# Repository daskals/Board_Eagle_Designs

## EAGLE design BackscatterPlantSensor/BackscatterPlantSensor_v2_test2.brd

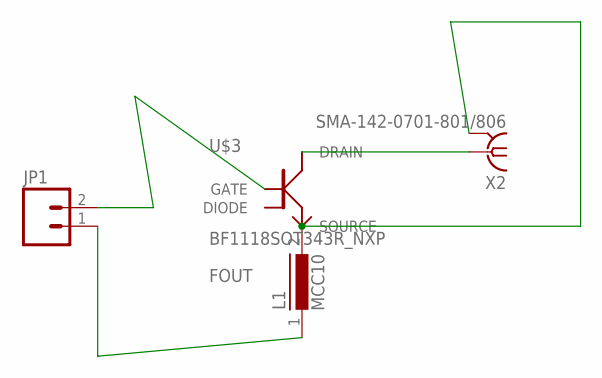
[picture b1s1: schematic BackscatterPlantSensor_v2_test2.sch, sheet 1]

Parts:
JP1: M02PTH; 1X02
L1: MCC10
U$3: BF1118SOT343R_NXP; SOT343R
X2: SMA-142-0701-801/806; J502-ND-142-0701-801/806

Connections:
DGND: JP1.2, U$3.1 (GATE)
DRAIN: U$3.4 (DRAIN), X2.1
FOUT: JP1.1, L1.1
FOUT2: L1.2, U$3.3 (SOURCE), X2.G@1 (GND)
GND: X2.G@2 (GND), X2.G@3 (GND), X2.G@4 (GND)

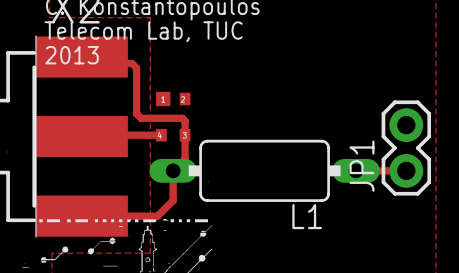
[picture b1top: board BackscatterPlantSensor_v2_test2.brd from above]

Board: 2 copper layers, 4 parts (0 on the bottom side), 5 nets.

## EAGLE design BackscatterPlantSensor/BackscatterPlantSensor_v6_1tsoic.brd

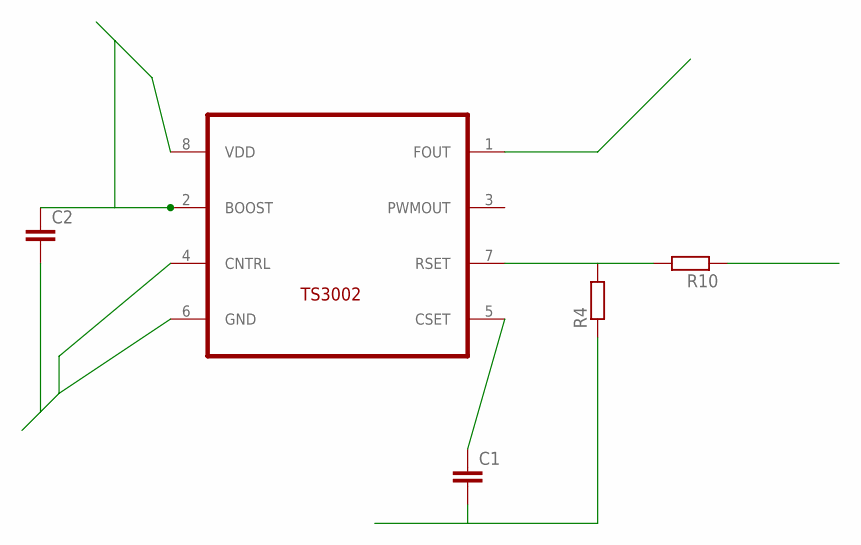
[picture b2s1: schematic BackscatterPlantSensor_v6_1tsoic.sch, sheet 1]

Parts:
C1, C2: CC0603; C0603
R4, R10: R-EU_R0603; R0603
U$1: TS3002; TDFN22-8

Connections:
DGND: C1.2, C2.2, R4.1, U$1.4 (CNTRL), U$1.6 (GND); also elsewhere on the board
FOUT: U$1.1 (FOUT); also elsewhere on the board
unnamed: C1.1, U$1.5 (CSET)
unnamed: R4.2, R10.2, U$1.7 (RSET)
VCOND: R10.1; also elsewhere on the board
VDD: C2.1, U$1.2 (BOOST), U$1.8 (VDD); also elsewhere on the board

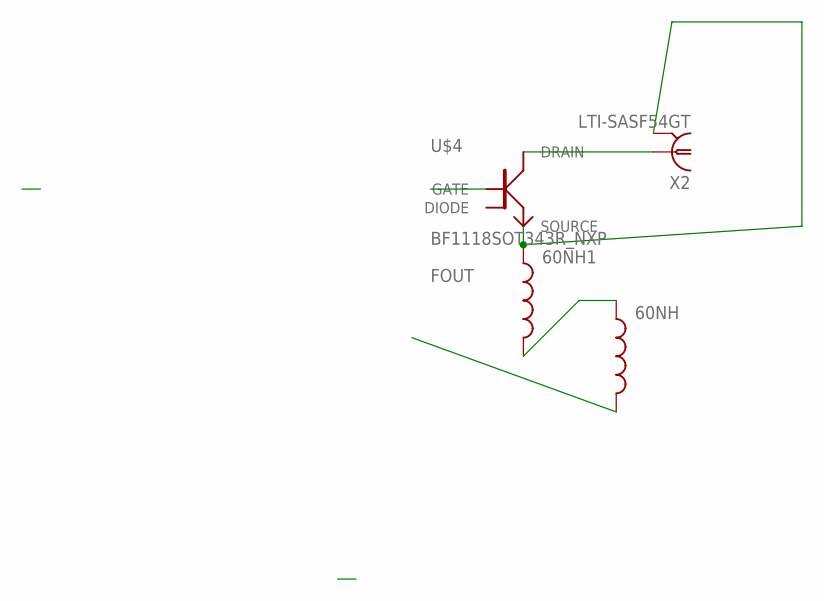
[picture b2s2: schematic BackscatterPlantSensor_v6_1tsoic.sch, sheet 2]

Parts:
60NH, 60NH1: INDUCTOR0402; C0402
U$4: BF1118SOT343R_NXP; SOT343R
X2: LTI-SASF54GT

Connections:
DGND: U$4.1 (GATE); also elsewhere on the board
DRAIN: U$4.4 (DRAIN), X2.1
FOUT: 60NH.2; also elsewhere on the board
FOUT2: 60NH1.1, U$4.3 (SOURCE), X2.2 (GND)
GND: X2.3 (GND), X2.4 (GND), X2.5 (GND); also elsewhere on the board
unnamed: 60NH.1, 60NH1.2

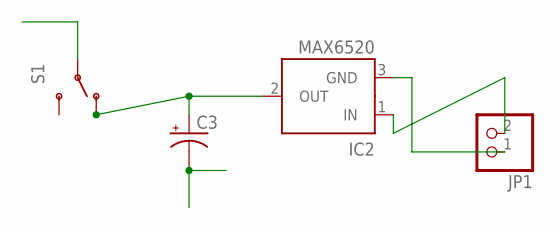
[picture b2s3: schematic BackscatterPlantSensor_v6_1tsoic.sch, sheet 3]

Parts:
C3: CAP_POL1206; EIA3216
IC2: MAX6520; SOT23
JP1: PINHD-1X2; 1X02
S1: SWITCH-SPDTPTH; SWITCH-SPDT

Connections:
GND: C3.C (-), IC2.3 (GND), JP1.1; also elsewhere on the board
unnamed: IC2.1 (IN), JP1.2
unnamed: C3.A (+), IC2.2 (OUT), S1.1 (O)
VDD: S1.2; also elsewhere on the board

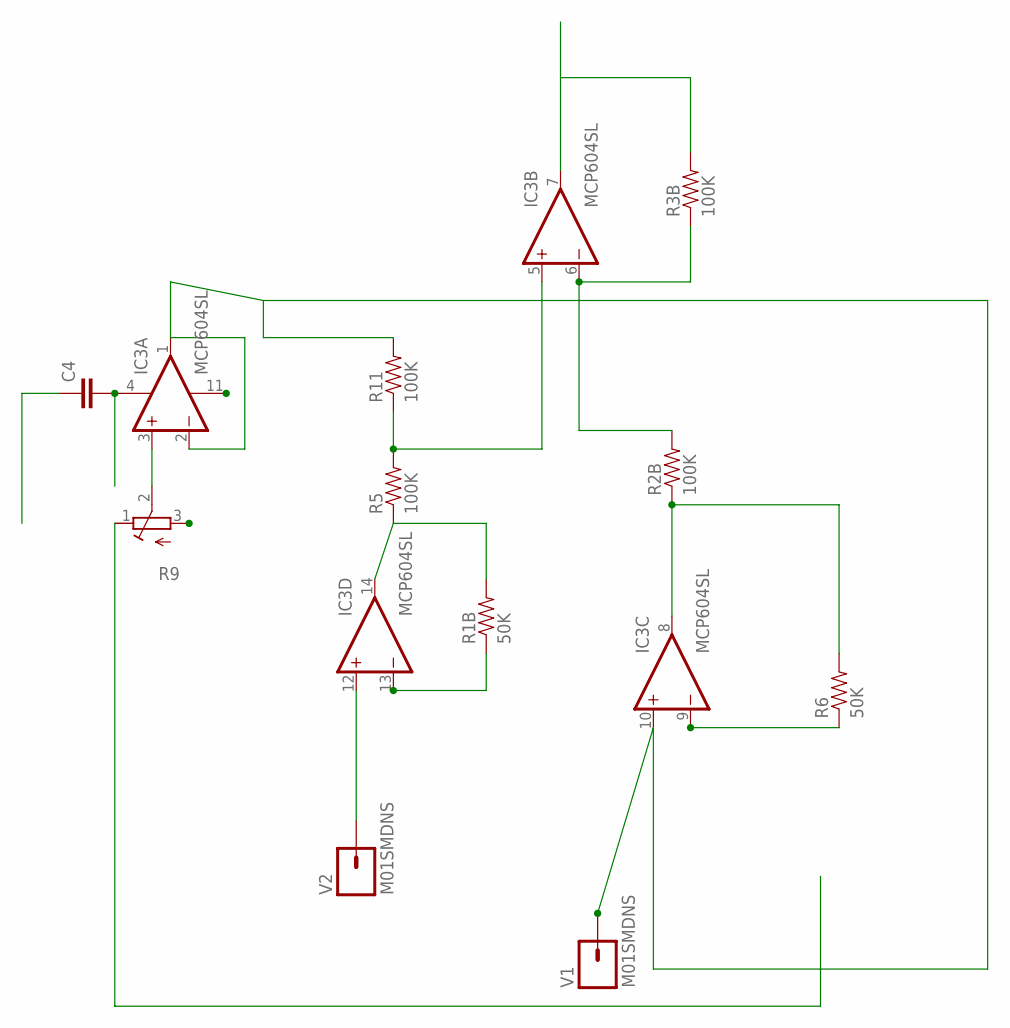
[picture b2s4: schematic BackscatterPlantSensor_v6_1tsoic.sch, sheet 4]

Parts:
C4: CAP0603-CAP; 0603-CAP
IC3: MCP604SL; SO14
R1B, R6: 50K; 0805
R2B, R3B, R5, R11: 100K; 0805
R9: R-TRIMM3314G; RTRIM3314G
V1, V2: M01SMDNS; 1X01NS

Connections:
AGND: C4.1, IC3.11 (V-), R9.3 (A)
unnamed: IC3.9 (-IN), R6.1
unnamed: IC3.8 (OUT), R2B.1, R6.2
unnamed: IC3.14 (OUT), R1B.2, R5.1
unnamed: IC3.6 (-IN), R2B.2, R3B.1
unnamed: IC3.12 (+IN), V2.1
unnamed: IC3.3 (+IN), R9.2 (S)
unnamed: IC3.13 (-IN), R1B.1
unnamed: IC3.5 (+IN), R5.2, R11.1
VCOND: IC3.7 (OUT), R3B.2; also elsewhere on the board
VDD: C4.2, IC3.4 (V+), R9.1 (E); also elsewhere on the board
VRF1: IC3.1 (OUT), IC3.2 (-IN), IC3.10 (+IN), R11.2, V1.1

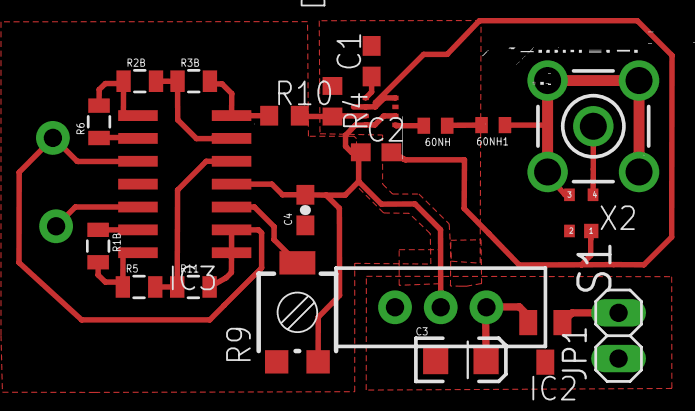
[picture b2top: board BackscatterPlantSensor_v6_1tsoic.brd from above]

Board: 2 copper layers, 24 parts (0 on the bottom side), 22 nets.

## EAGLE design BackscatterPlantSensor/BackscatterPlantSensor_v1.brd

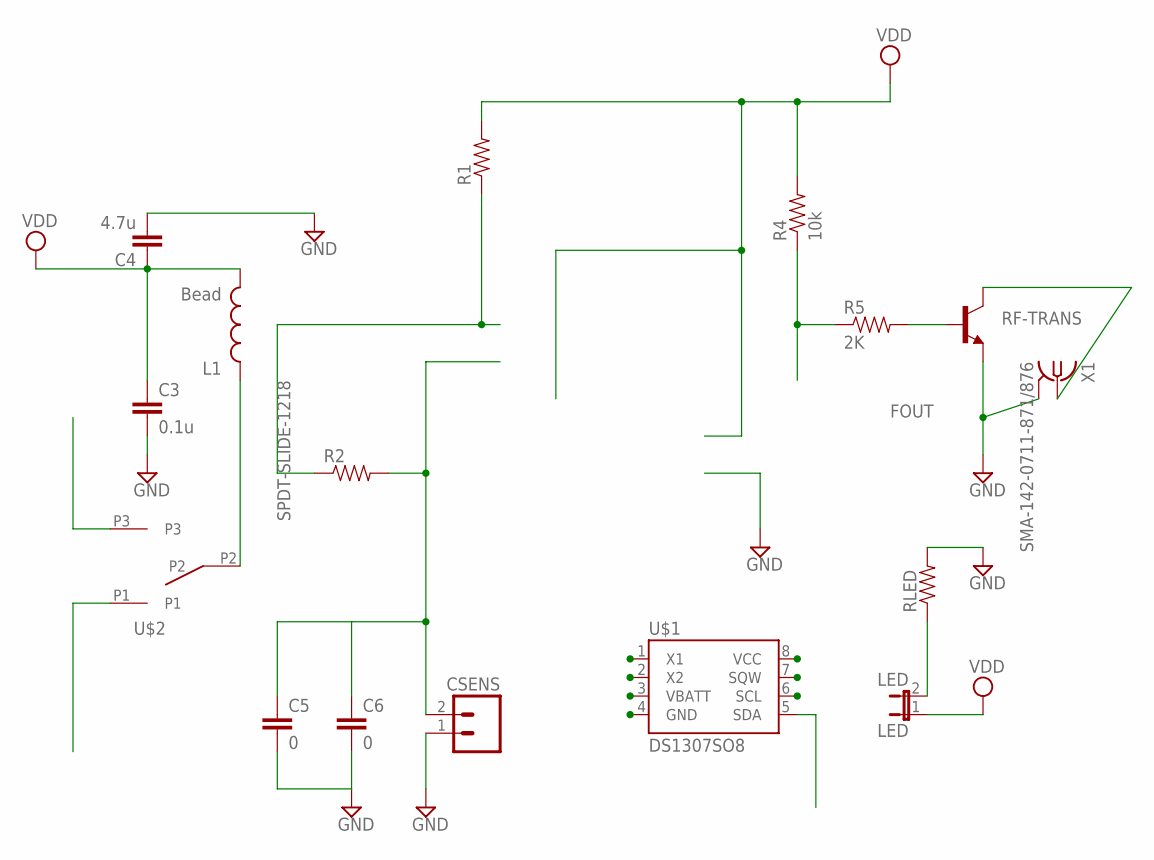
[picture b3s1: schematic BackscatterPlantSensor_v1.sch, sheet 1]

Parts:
C3: 0.1u; 0603-CAP
C4: 4.7u; 0805
C5, C6: 0; 0603-CAP
CSENS: M02PTH; 1X02
L1: Bead; C0402
LED: LED; 1X02_LOCK
R1: RESISTOR0805-RES; 0805
R2: RESISTOR0603-RES; 0603-RES
R4: 10k; 0805
R5: 2K; 0805
RF-TRANS: TRANSISTOR_NPNSOT23; SOT23
RLED: RESISTOR0805-RES; 0805
U$1: DS1307SO8; SO08
U$2: SPDT-SLIDE-1218
X1: SMA-142-0711-871/876; J502-ND-142-0711-871/876

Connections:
DGND: C3.2, C4.2, C5.2, C6.2, CSENS.1, RF-TRANS.2 (E), RLED.2, U$1.1 (X1), X1.G@1 (GND), X1.G@2 (GND), X1.G@3 (GND), X1.G@4 (GND)
FOUT: R4.1, R5.1, U$1.3 (VBATT)
unnamed: LED.2, RLED.1
unnamed: RF-TRANS.3 (C), X1.1
unnamed: R5.2, RF-TRANS.1 (B)
P2: C5.1, C6.1, CSENS.2, R2.2, U$1.2 (X2), U$1.6 (SCL)
P5: U$1.5 (SDA); also elsewhere on the board
P7: R1.1, R2.1, U$1.7 (SQW)
POWER: U$2.P1; also elsewhere on the board
POWEROUT: L1.1, U$2.P2; also elsewhere on the board
VDD: C3.1, C4.1, L1.2, LED.1, R1.2, R4.2, U$1.4 (GND), U$1.8 (VCC)

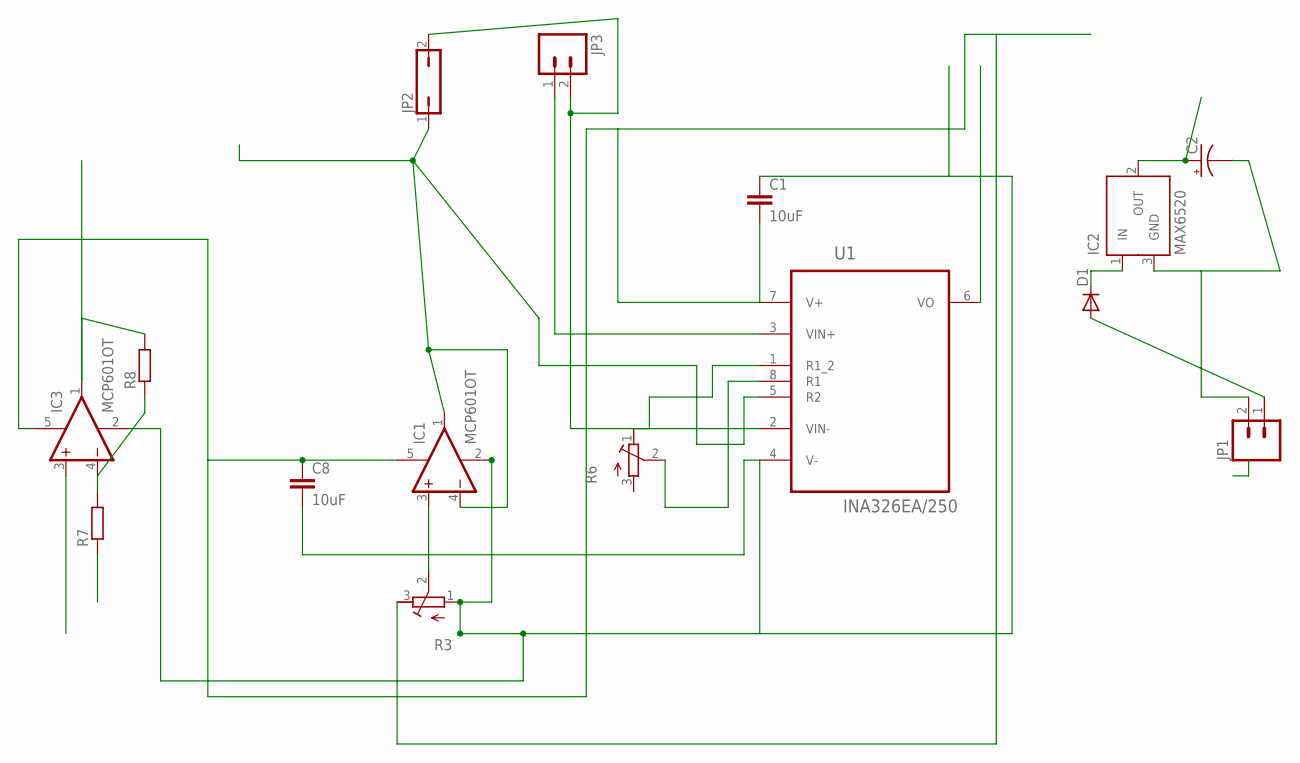
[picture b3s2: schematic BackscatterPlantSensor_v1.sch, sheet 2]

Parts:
C1, C8: 10uF; 0805
C2: CAP_POLPTH1; CPOL-RADIAL-100UF-25V
D1: DIODESOD523; SOD523
IC1, IC3: MCP601OT; SOT23-5
IC2: MAX6520; SOT23
JP1, JP3: M02PTH; 1X02
JP2: JP1Q; JP1
R3: R-TRIMM3314J; RTRIM3314J
R6: R-TRIMM3314G; RTRIM3314G
R7, R8: R-EU_R0603; R0603
U1: INA326EA/250; SOP65P490X110-8N

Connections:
AGND: C1.1, C8.2, IC1.2 (V-), IC3.2 (V-), R3.1 (E), R7.1, U1.4 (V-)
GND: C2.2 (-), IC2.3 (GND), JP1.2
IN: D1.C, IC2.1 (IN)
unnamed: IC1.3 (+IN), R3.2 (S)
unnamed: JP2.2, JP3.2, U1.2 (VIN-)
unnamed: JP3.1, U1.3 (VIN+)
unnamed: R6.2 (S), U1.8 (R1)
unnamed: R6.1 (E), U1.1 (R1_2)
unnamed: D1.A, JP1.1
unnamed: IC3.4 (-IN), R7.2, R8.1
P5: IC3.1 (OUT), R8.2; also elsewhere on the board
POWER: C2.1 (+), IC2.2 (OUT); also elsewhere on the board
POWEROUT: C1.2, C8.1, IC1.5 (V+), IC3.5 (V+), R3.3 (A), U1.7 (V+); also elsewhere on the board
VOUT1: IC3.3 (+IN), U1.6 (VO)
VREF: IC1.1 (OUT), IC1.4 (-IN), JP2.1, U1.5 (R2)

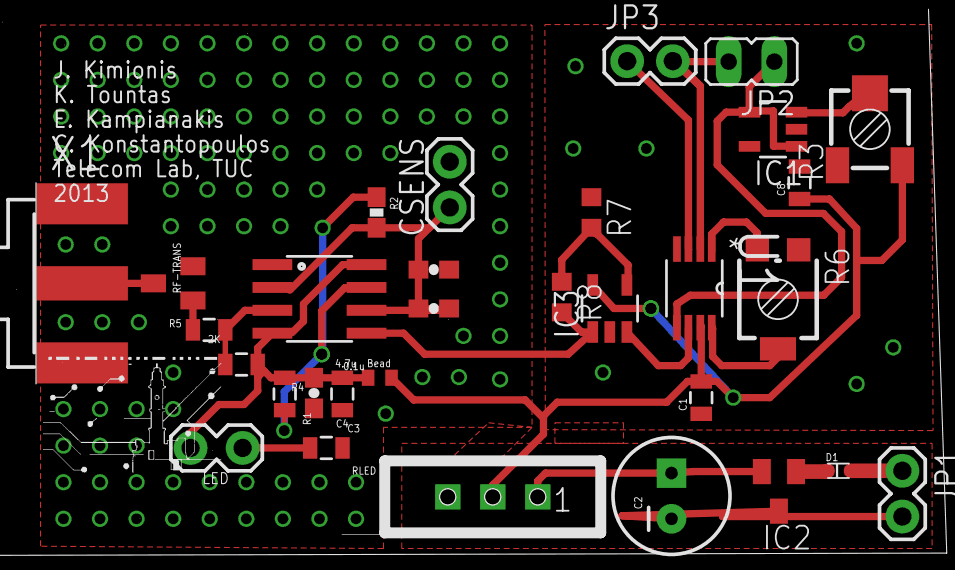
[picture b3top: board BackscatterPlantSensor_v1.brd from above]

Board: 2 copper layers, 31 parts (0 on the bottom side), 23 nets.

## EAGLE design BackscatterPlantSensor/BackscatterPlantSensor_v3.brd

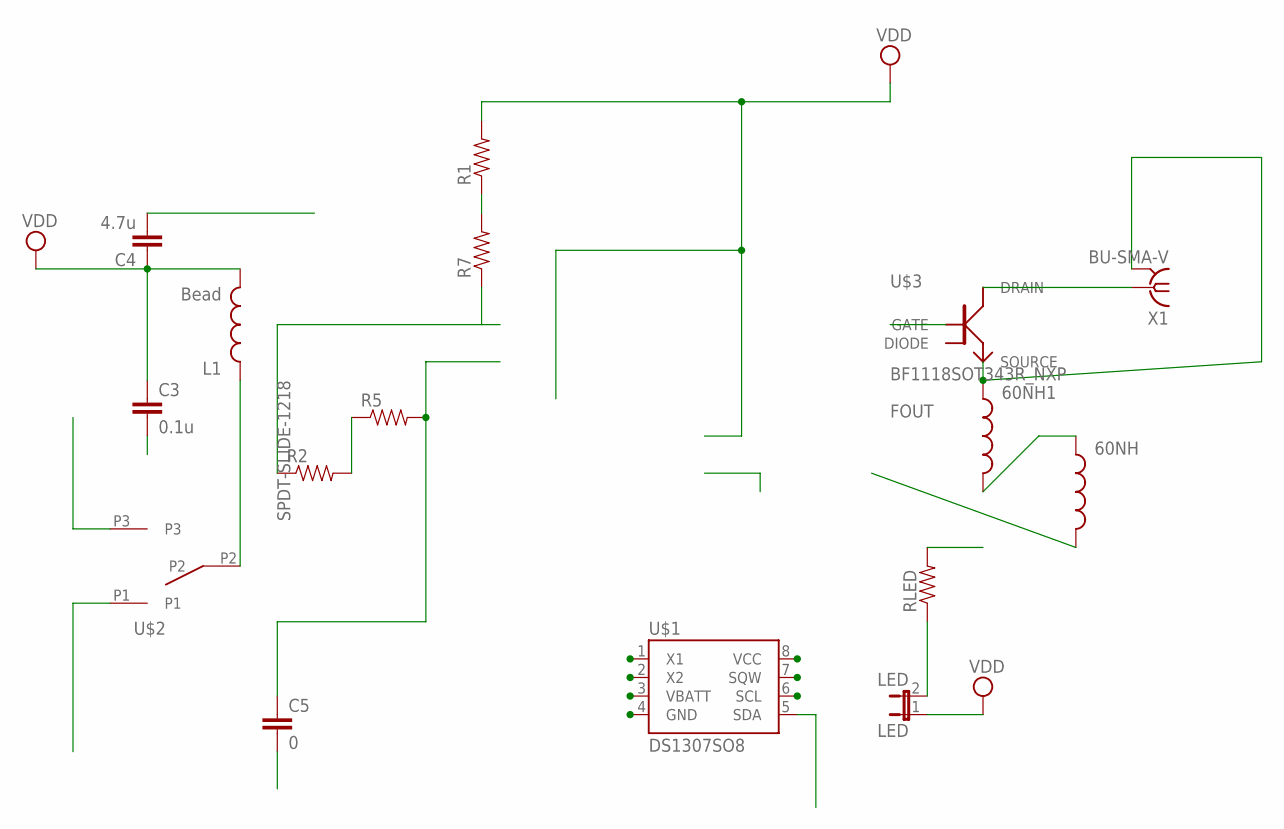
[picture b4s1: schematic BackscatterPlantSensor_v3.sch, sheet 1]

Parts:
60NH, 60NH1: INDUCTOR0402; C0402
C3: 0.1u; 0603-CAP
C4: 4.7u; 0805
C5: 0; 0603-CAP
L1: Bead; C0402
LED: LED; 1X02_LOCK
R1, R7: RESISTOR0805-RES; 0805
R2, R5: RESISTOR0603-RES; 0603-RES
RLED: RESISTOR0805-RES; 0805
U$1: DS1307SO8; SO08
U$2: SPDT-SLIDE-1218
U$3: BF1118SOT343R_NXP; SOT343R
X1: BU-SMA-V

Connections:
DGND: C3.2, C4.2, C5.2, RLED.2, U$1.1 (X1), U$3.1 (GATE)
DRAIN: U$3.4 (DRAIN), X1.1
FOUT: 60NH.2, U$1.3 (VBATT)
FOUT2: 60NH1.1, U$3.3 (SOURCE), X1.2 (GND)
GND: X1.3 (GND), X1.4 (GND), X1.5 (GND); also elsewhere on the board
unnamed: 60NH.1, 60NH1.2
unnamed: LED.2, RLED.1
unnamed: R1.1, R7.2
unnamed: R2.2, R5.1
P6: C5.1, R5.2, U$1.2 (X2), U$1.6 (SCL)
P7: R2.1, R7.1, U$1.7 (SQW)
POWER: U$2.P1; also elsewhere on the board
POWEROUT: L1.1, U$2.P2; also elsewhere on the board
VDD: C3.1, C4.1, L1.2, LED.1, R1.2, U$1.4 (GND), U$1.8 (VCC)
VOUT1: U$1.5 (SDA); also elsewhere on the board

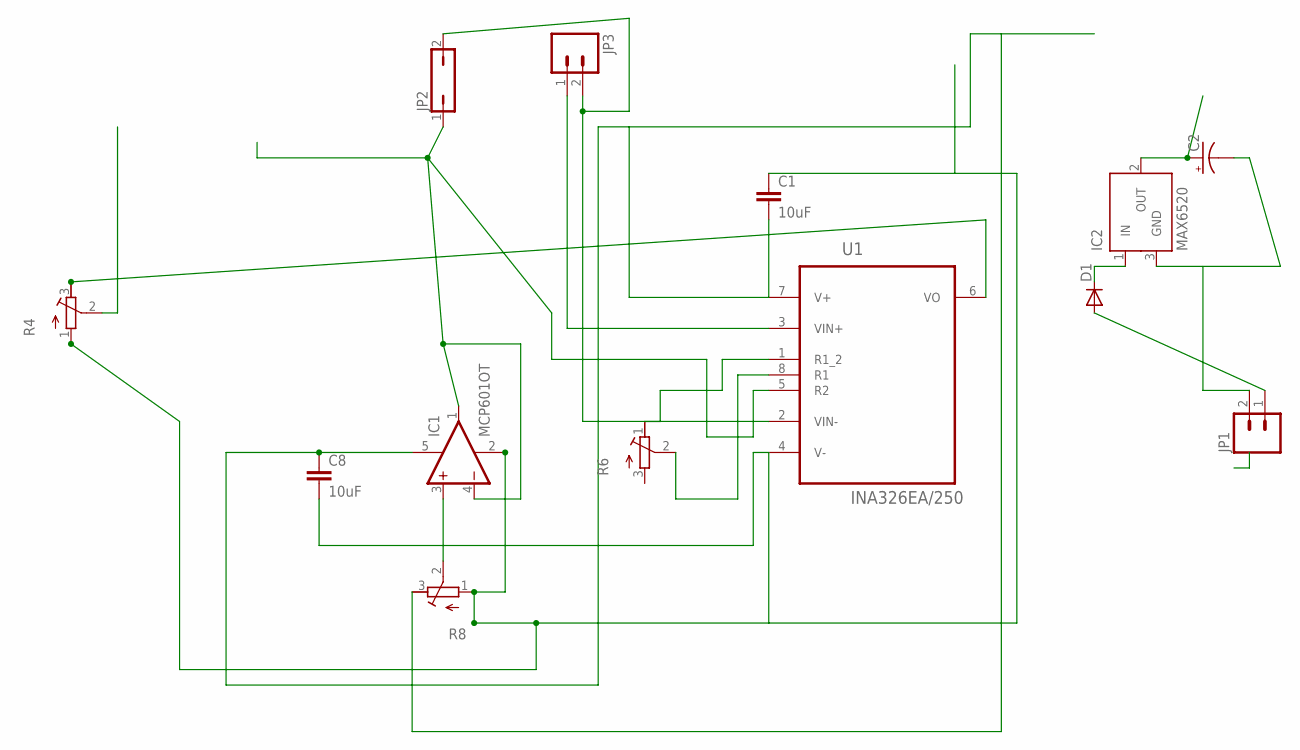
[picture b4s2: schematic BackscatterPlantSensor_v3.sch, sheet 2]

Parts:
C1, C8: 10uF; 0805
C2: CAP_POLPTH1; CPOL-RADIAL-100UF-25V
D1: DIODESOD523; SOD523
IC1: MCP601OT; SOT23-5
IC2: MAX6520; SOT23
JP1, JP3: M02PTH; 1X02
JP2: JP1Q; JP1
R4, R8: R-TRIMM74W; RTRIM74W
R6: R-TRIMM3314G; RTRIM3314G
U1: INA326EA/250; SOP65P490X110-8N

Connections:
AGND: C1.1, C8.2, IC1.2 (V-), R4.1 (E), R8.1 (E), U1.4 (V-)
GND: C2.2 (-), IC2.3 (GND), JP1.2; also elsewhere on the board
IN: D1.C, IC2.1 (IN)
unnamed: IC1.3 (+IN), R8.2 (S)
unnamed: JP2.2, JP3.2, U1.2 (VIN-)
unnamed: JP3.1, U1.3 (VIN+)
unnamed: R6.2 (S), U1.8 (R1)
unnamed: R6.1 (E), U1.1 (R1_2)
unnamed: D1.A, JP1.1
POWER: C2.1 (+), IC2.2 (OUT); also elsewhere on the board
POWEROUT: C1.2, C8.1, IC1.5 (V+), R8.3 (A), U1.7 (V+); also elsewhere on the board
VOUT1: R4.2 (S); also elsewhere on the board
VOUT12: R4.3 (A), U1.6 (VO)
VREF: IC1.1 (OUT), IC1.4 (-IN), JP2.1, U1.5 (R2)

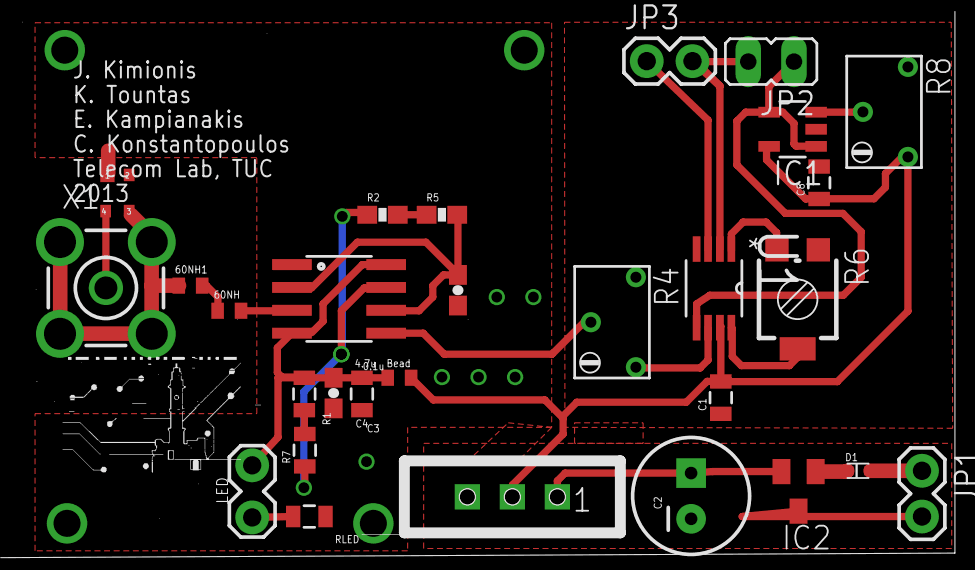
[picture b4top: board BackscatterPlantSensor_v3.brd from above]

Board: 2 copper layers, 29 parts (0 on the bottom side), 25 nets.

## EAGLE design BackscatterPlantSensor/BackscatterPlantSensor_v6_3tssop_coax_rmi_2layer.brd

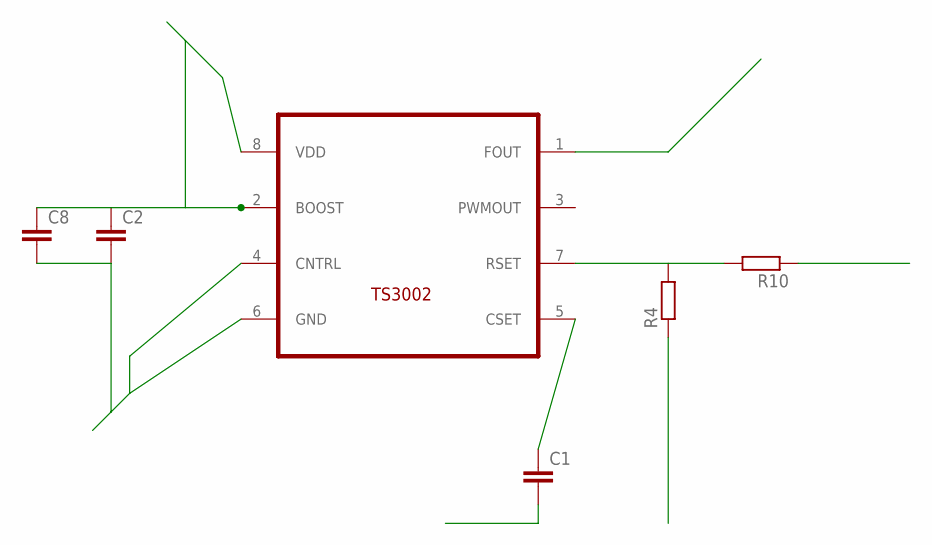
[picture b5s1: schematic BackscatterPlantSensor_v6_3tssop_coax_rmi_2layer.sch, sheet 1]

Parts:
C1, C2, C8: CC0603; C0603
R4, R10: R-EU_R0603; R0603
U$1: TS3002; TDFN22-8

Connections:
AGND: R4.1; also elsewhere on the board
DGND: C1.2, C2.2, C8.2, U$1.4 (CNTRL), U$1.6 (GND); also elsewhere on the board
FOUT: U$1.1 (FOUT); also elsewhere on the board
unnamed: C1.1, U$1.5 (CSET)
unnamed: R4.2, R10.2, U$1.7 (RSET)
VCOND: R10.1; also elsewhere on the board
VDD: C2.1, C8.1, U$1.2 (BOOST), U$1.8 (VDD); also elsewhere on the board

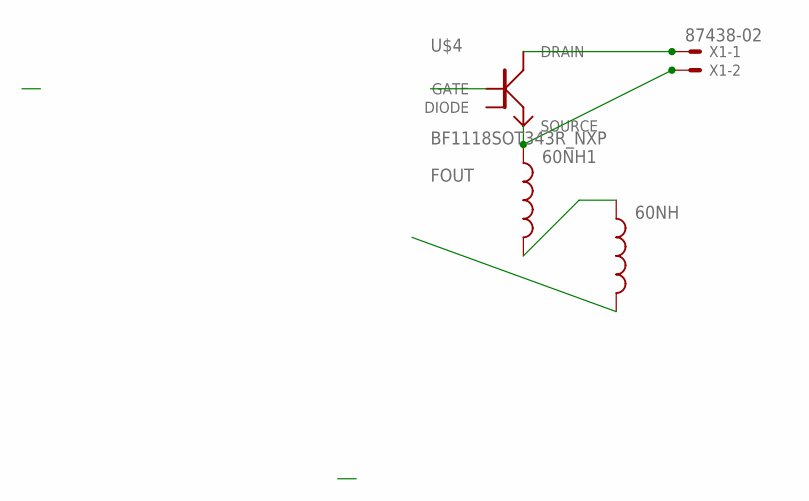
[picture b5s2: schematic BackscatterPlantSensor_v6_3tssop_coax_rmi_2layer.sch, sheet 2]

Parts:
60NH, 60NH1: INDUCTOR0402; C0402
U$4: BF1118SOT343R_NXP; SOT343R
X1: 87438-02

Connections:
DGND: U$4.1 (GATE); also elsewhere on the board
FOUT: 60NH.2; also elsewhere on the board
unnamed: 60NH.1, 60NH1.2
RF_MINUS: 60NH1.1, U$4.3 (SOURCE), X1.2
RF_PLUS: U$4.4 (DRAIN), X1.1

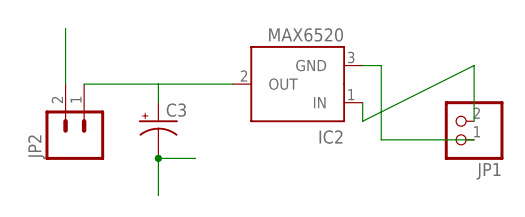
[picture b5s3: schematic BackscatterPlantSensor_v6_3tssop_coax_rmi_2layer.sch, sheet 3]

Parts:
C3: CAP_POL1206; EIA3216
IC2: MAX6520; SOT23
JP1: PINHD-1X2; 1X02
JP2: M02LOCK; 1X02_LOCK

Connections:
GND: C3.C (-), IC2.3 (GND), JP1.1
unnamed: IC2.1 (IN), JP1.2
unnamed: C3.A (+), IC2.2 (OUT), JP2.1
VDD: JP2.2; also elsewhere on the board

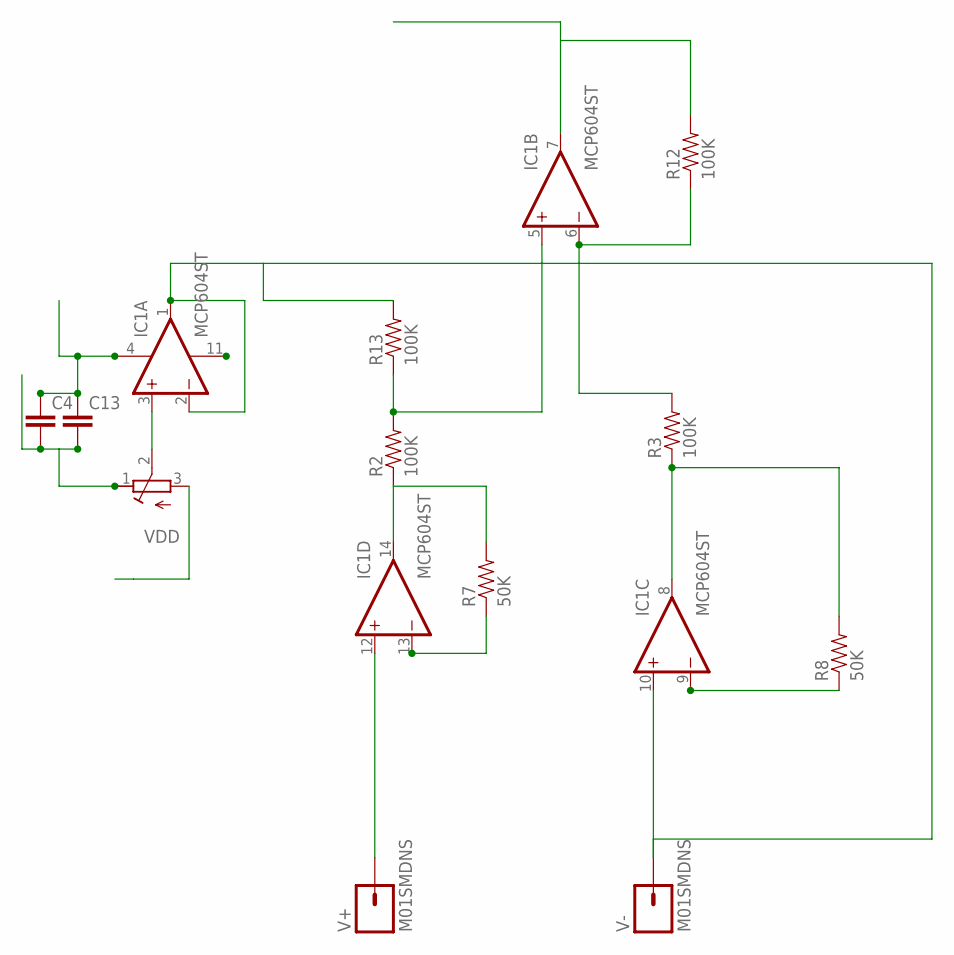
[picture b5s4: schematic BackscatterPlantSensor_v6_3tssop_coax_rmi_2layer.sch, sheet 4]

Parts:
C4, C13: CAP0603-CAP; 0603-CAP
IC1: MCP604ST; TSSOP14
R2, R3, R12, R13: 100K; 0805
R7, R8: 50K; 0805
V+: M01SMDNS; 1X01NS
V-: M01SMDNS; 1X01NS
VDD: R-TRIMM3314G; RTRIM3314G

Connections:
AGND: C4.2, C13.2, IC1.11 (V-), VDD.1 (E); also elsewhere on the board
unnamed: IC1.9 (-IN), R8.1
unnamed: IC1.8 (OUT), R3.1, R8.2
unnamed: IC1.14 (OUT), R2.1, R7.2
unnamed: IC1.6 (-IN), R3.2, R12.1
unnamed: IC1.3 (+IN), VDD.2 (S)
unnamed: IC1.13 (-IN), R7.1
unnamed: IC1.5 (+IN), R2.2, R13.1
V+: IC1.12 (+IN), V+.1
VCOND: IC1.7 (OUT), R12.2; also elsewhere on the board
VDD: C4.1, C13.1, IC1.4 (V+), VDD.3 (A); also elsewhere on the board
VRF: IC1.1 (OUT), IC1.2 (-IN), IC1.10 (+IN), R13.2, V-.1

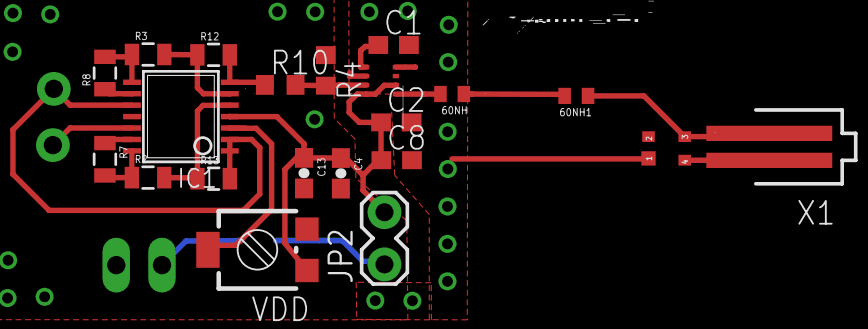
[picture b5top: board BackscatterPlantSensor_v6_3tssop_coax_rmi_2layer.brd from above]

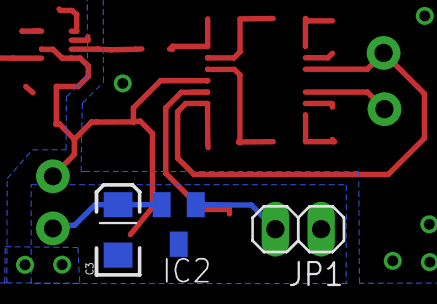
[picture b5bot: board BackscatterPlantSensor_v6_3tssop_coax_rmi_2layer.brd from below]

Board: 2 copper layers, 26 parts (3 on the bottom side), 22 nets.

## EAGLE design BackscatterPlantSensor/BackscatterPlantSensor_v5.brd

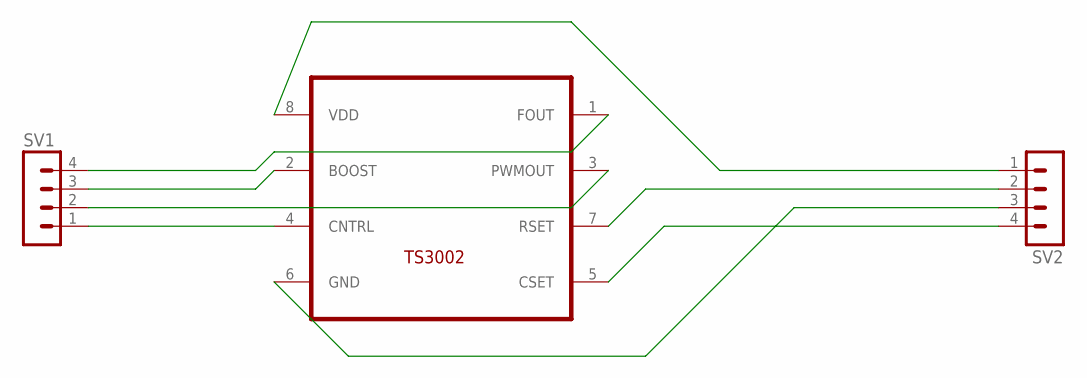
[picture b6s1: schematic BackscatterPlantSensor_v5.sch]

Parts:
SV1, SV2: MA04-1
U$1: TS3002; TDFN22-8

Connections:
unnamed: SV1.1, U$1.4 (CNTRL)
unnamed: SV1.2, U$1.3 (PWMOUT)
unnamed: SV1.3, U$1.2 (BOOST)
unnamed: SV1.4, U$1.1 (FOUT)
unnamed: SV2.1, U$1.8 (VDD)
unnamed: SV2.2, U$1.7 (RSET)
unnamed: SV2.3, U$1.6 (GND)
unnamed: SV2.4, U$1.5 (CSET)

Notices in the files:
parts and their libraries:
SparkFun-Resistors: Licensing: CC v3.0 Share-Alike You are welcome to use this library for commercial purposes.
